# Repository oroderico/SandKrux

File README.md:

Este repositório é um fork do projeto original criado por [sandman21vs](https://github.com/sandman21vs).

Repositório original:
https://github.com/sandman21vs/SandKrux

Crédito integral ao autor original. Este mirror foi publicado para fins de preservação/disponibilidade do projeto.

Todas as licenças, créditos e avisos originais foram mantidos.
 
# SandKrux

Placa de desenvolvimento baseada no chip **K210**, com entradas para **touch**, **câmera** e **LCD grande**, criada especificamente para rodar o firmware **Krux**.

## Status do projeto
**Em desenvolvimento — não finalizado.**  
Este repositório está em evolução. Mudanças podem ocorrer sem aviso.

## Foto da placa
Coloque a imagem em `docs/placa.jpg` (ou ajuste o caminho abaixo).

## Firmware alvo
Este hardware está sendo desenvolvido para o firmware Krux:
- https://github.com/selfcustody/krux

## Como colaborar
Contribuições da comunidade são muito bem-vindas.  
Abra issues, discuta melhorias e proponha alterações.

## Licença
GPLv3.

## Nota sobre fabricação e apoio ao Krux
Se no futuro você pretender **fabricar e vender** este dispositivo, fica o pedido de doar **ao menos 1%** do valor dos dispositivos para a equipe de desenvolvimento do Krux.  
Este é um projeto open-source e, sem o trabalho deles, nada disso existiria.

## Agradecimentos
Obrigado à comunidade e à equipe do Krux pelo trabalho que torna este projeto possível.

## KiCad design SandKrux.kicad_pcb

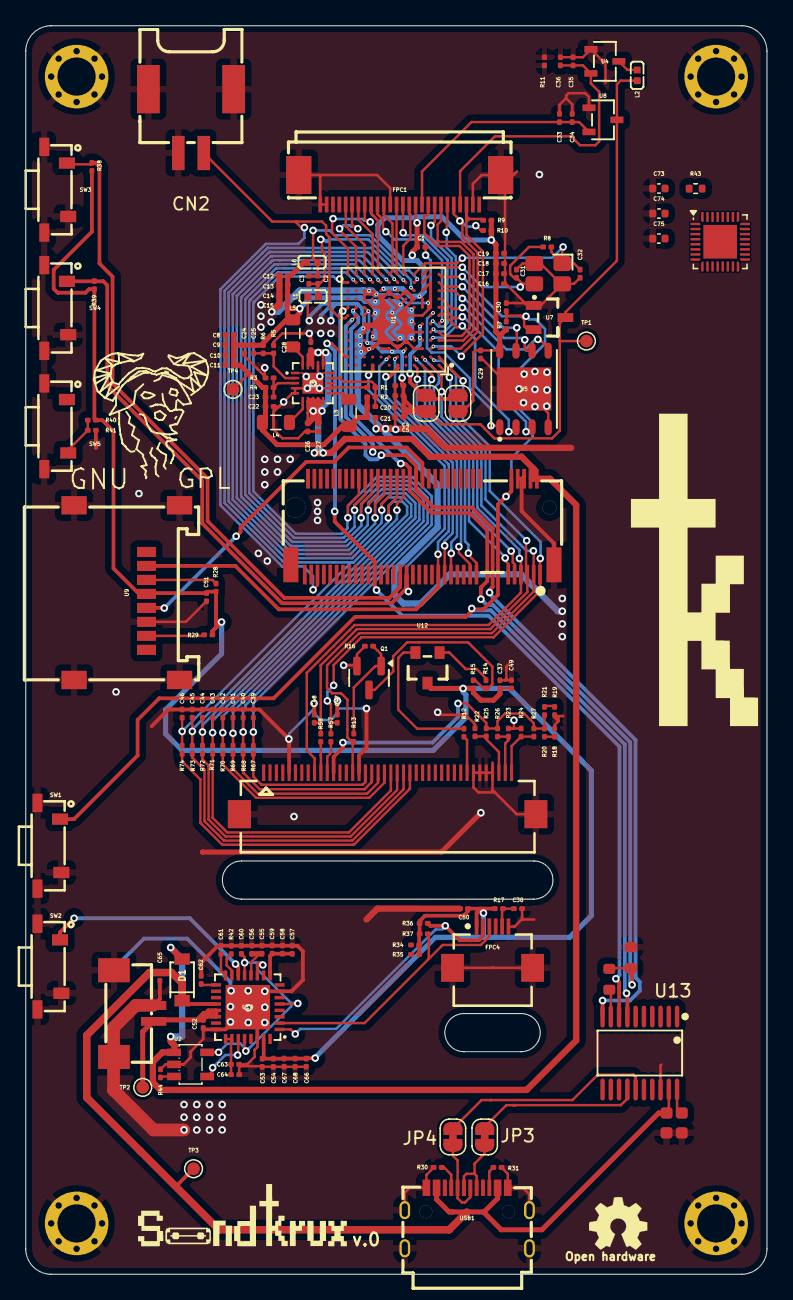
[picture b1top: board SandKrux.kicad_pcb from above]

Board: 2 copper layers, 58.3 x 98.2 mm, 173 parts (0 on the bottom side), 118 nets.

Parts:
C1, C60, C62: 1uF; C_0201_0603Metric
C2, C4, C5, C6, C7, C18, C19, C29, C30, C34, C38, C49, C56: 100nF; C_0201_0603Metric
C3, C8, C9, C10, C11, C12, C13, C14, C15, C16, C17, C33, C36, C37, C50, C51, C53, C55, C58, C65: 10uF; C_0201_0603Metric
C20, C23, C25: 18pF; C_0201_0603Metric
C21, C22, C24, C26, C27, C28, C35, C52, C57, C59, C64, C66, C67, C68: 22uF; C_0201_0603Metric
C31, C32: 6pF; C_0201_0603Metric
C39, C40, C41, C42, C43, C44, C45, C46, C47, C48: 100pF; C_0201_0603Metric
C54: 1nF; C_0201_0603Metric
C61: 220uF; C_0201_0603Metric
C63: 220nF; C_0201_0603Metric
C73, C74, C75: 100n; C_0402_1005Metric
C77: 22uF; C_0603
C79: 10uF; C_0603
CN2: SM02B-PASS-TBT(LF)(SN); CONN-SMD_SM02B-PASS-TBT
CN3: 1.25mm-2P socket; CONN-SMD_1.25T-2P
D1: 1N5819HW-7-F; SOD-123_L2.7-W1.6-LS3.7-RD
FPC1: 05A20L26P; FPC-SMD_05A20L26P
FPC3: FH12-40S-0.5SH(55); FPC-SMD_FH12-40S-0.5SH-55
FPC4: FH12-6S-0.5SH(55); FPC-SMD_FH12-6S-0.5SH-55
H1, H2, H3, H4: Hole, 3mm
IC1: TROPIC01_chip; QFN-32-1EP_4x4mm_P0.4mm_EP2.65x2.65mm
JP1, JP2: SolderJumper_2_Open; SolderJumper-2_P1.3mm_Open_RoundedPad1.0x1.5mm
JP3, JP4: SolderJumper_2_Bridged; SolderJumper-2_P1.3mm_Bridged_RoundedPad1.0x1.5mm
L1, L2, L6: CBW100505U601T; L0402
L3, L4, L5: 2.2uH; L_0805_2012Metric
Q1: S8050; Q_SOT-23
R1, R6: 300k 1%; R_0201_0603Metric
R2, R3, R5: 150k 1%; R_0201_0603Metric
R4: 680k 1%; R_0201_0603Metric
R7: 12K; R_0201_0603Metric
R8: 1M; R_0201_0603Metric
R9, R10: 2K; R_0201_0603Metric
R11, R18, R21, R41: 0R; R_0201_0603Metric
R12: 5.1R; R_0201_0603Metric
R13, R14, R57, R58, R67, R68, R69, R70, R71, R72, R73, R74: 100R; R_0201_0603Metric
R15, R16, R17, R28, R29, R44: 10K; R_0201_0603Metric
R19, R20, R22, R23, R27, R40: NC; R_0201_0603Metric
R24, R25, R26, R30, R31: 5.1K; R_0201_0603Metric
R32, R33: 1kΩ; R_0603
R34, R35, R36, R37, R38, R39: 1.5K; R_0201_0603Metric
R42: 200K; R_0201_0603Metric
R43: 47k; R_0402_1005Metric
SW1, SW2, SW3, SW4, SW5: TL3330AF130QG; SW-SMD_E-SWITCH_TL3330
Sign_OSHW_7.3x6.0mm: Sign_OSHW_7.3x6.0mm; Sign_OSHW_7.3x6.0mmn
TP1, TP2, TP3, TP4: TestPoint_Small; TestPoint_Pad_D1.0mm
U1: K210_C913414; BGA-144_L8.0-W8.0-R12-C12-P0.65-BL
U2: MT9700; SOT-23-5_L3.0-W1.7-P0.95-LS2.8-BR
U3: XC6206-3.3V; SSOT-3_L2.9-W1.6-P0.95-LS2.8-BR
U4: XC6206P182MR_C347373; SOT-23-3_L3.0-W1.7-P0.95-LS2.9-BR
U5: GD25LQ128EWIGR; WSON-8_L6.0-W5.0-P1.27-BL-EP
U6: TMI7003C; QFN-20_L3.0-W3.0-P0.40-BL-EP1.7
U7: SGM803-TXN3/TR_C5152602; SOT-23-3_L2.9-W1.5-P1.90-LS2.6-BR
U8: XC6206P302MR_C347375; SOT-23-3_L3.0-W1.7-P0.95-LS2.9-BR
U9: HX TF-CARD XG8P H1.5; TF-SMD_HX-TF-CARD-XG8P-H1.5
U10: AXP173_C3345106; QFN-32_L5.0-W5.0-P0.50-TL-EP3.5-1
U12: PCIE-67P42H; PCIE-SMD_75P-P0.50_HYC01B-05NGFF-420
U13: CH552T; TSSOP-20_L6.5-W4.4-P0.65-LS6.4-BL
USB1: HYCW412-USBC16-065B; USB-C-SMD_HYCW412-USBC16-065B
X1: X322526MMB4SI; CRYSTAL-SMD_4P-L3.2-W2.5-BL

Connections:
+3.3V: C4.2, C5.2, C6.2, C7.2, JP2.1 (A), L2.2, TP1.1, U1.C5 (VDDIO5B), U1.C7 (VDDIO4B), U1.C8 (VDDIO3B), U1.D10 (VDDIO2A), U1.G10 (VDDIO1A), U1.H10 (VDDIO0A), U7.3 (VCC), U8.3 (VIN)
/3V3: C37.1, C49.1, C50.1, C51.2, C53.2, C54.2, C66.2, C67.2, C68.2, FPC4.1, R15.2, R17.1, R28.2, R29.2, R34.2, R35.2, R36.1, R37.1, R38.1, R39.1, R40.2, U3.3 (VIN), U9.4 (VDD), U10.31 (DCDC1)
/5V: C26.2, C27.2, C28.2, D1.2 (A), U2.1 (VOUT), U6.7 (VIN2), U6.8 (EN2), U6.9 (EN1), U6.10 (VIN1), U6.16 (NC), U6.18 (EN3), U6.19 (VIN3), U12.2, U12.4
/5V_USB: C65.1, C79.1, D1.1 (K), TP3.1, U10.20 (ACIN), U13.19 (VCC/VDD), USB1.A4B9 (VBUS), USB1.B4A9 (VBUS)
/ADD_3V0: C57.2, C58.2, C59.2, U10.9 (LDO3)
/BOOT: U1.B12 (IO_16), U12.53, U13.8 (P1.1/T2EX/CAP2/TIN1/VBUS2/AIN0)
/CAPTOUCH_RST: C38.1, FPC4.5, R17.2
/CC1_2: R30.2, USB1.A5 (CC1)
/CC2_2: R31.2, USB1.B5 (CC2)
/CH552_P1.0: C30.2, R7.2, SW1.1, U1.M1 (~RESET), U7.2 (~RESET), U12.10, U13.7 (P1.0/T2/CAP1/TIN0)
/CH552_RX0: U1.H12 (IO_5), U12.40, U13.10 (P3.0/PWM1_/RXD)
/CH552_TX0: R32.1, U13.9 (P3.1/PWM2_/TXD)
/EXTEN: U2.4 (EN), U10.27 (EXTEN)
/I2C_SCL: FPC4.3, R37.2, U10.2 (SCK)
/I2C_SDA: FPC4.2, R36.2, U10.1 (SDA)
/I2S2_SDI: U1.A3 (IO_35), U12.11
/I2S2_SDOD: U1.B3 (IO_34), U12.9
/IM0: FPC3.38, R22.1, R25.1
/IM1: FPC3.39, R23.1, R26.1
/IM2: FPC3.40, R24.1, R27.1
/IPSOUT: C60.1, U2.5 (VIN), U10.5 (VIN2), U10.11 (LDOIN), U10.13 (APS), U10.28 (VIN1)
/ISET: R44.2, U2.3 (SET)
/ISP_RX: R32.2, R33.1, U1.H11 (IO_4), U12.42
/KEY1: R39.2, SW4.1, U1.A9 (IO_23), U12.43
/KEY2: R38.2, SW3.1, U12.45
/LCD_BACKLIGHT: R12.2, U3.2 (VOUT)
/LCD_CS: FPC3.9, U1.A2 (IO_36), U12.7
/LCD_D0: C39.1, R67.2, U1.L12 (SPI0_D0), U12.58
/LCD_D1: C40.1, R68.2, U1.L11 (SPI0_D1), U12.56
/LCD_D2: C41.1, R69.2, U1.L10 (SPI0_D2), U12.54
/LCD_D3: C42.1, R70.2, U1.L9 (SPI0_D3), U12.52
/LCD_D4: C43.1, R71.2, U1.L8 (SPI0_D4), U12.50
/LCD_D5: C44.1, R72.2, U1.L7 (SPI0_D5), U12.48
/LCD_D6: C45.1, R73.2, U1.L6 (SPI0_D6), U12.46
/LCD_D7: C46.1, R74.2, U1.L5 (SPI0_D7), U12.44
/LCD_DC: C48.1, R58.2, U1.B2 (IO_38), U12.5
/LCD_RST: FPC3.15, R13.1, U1.A1 (IO_37), U12.3
/LCD_WR: C47.1, R57.2, U1.B1 (IO_39), U12.1
/PIN21: U1.B4 (IO_32), U12.21
/PIN23: U1.A4 (IO_33), U12.23
/PRINTER: CN2.1, U1.G12 (IO_7), U12.71
/PWRON: SW2.1, U10.14 (PWRON)
/SPI1_CS_TF: U1.B7 (IO_26), U9.2 (CD/DAT3), U12.33
/SPI1_MISO: U1.G11 (IO_6), U9.5 (CLK), U12.38
/SPI1_MOSI: R28.1, U9.3 (CMD)
/USBDM: JP4.1 (A), USB1.A7 (DN1), USB1.B7 (DN2)
/USBDP: JP3.1 (A), USB1.A6 (DP1), USB1.B6 (DP2)
/USB_D+: U1.B6 (IO_28), U12.29
/USB_D-: U1.A6 (IO_29), U12.31
/VBAT: C52.2, CN3.1, TP2.1, U10.21 (BAT), U10.22 (BAT)
/VCC_1V83V3: FPC3.12, R20.2, R21.2, R25.2, R26.2, R27.2
/VCC_6: R18.1, R20.1
/VCC_7: R19.1, R21.1
/VDD: C55.1, C56.1, U10.12 (LDO4)
/k210/0V9: C8.2, C9.2, C10.2, C11.2, C12.2, C13.2, C14.2, C15.2, C20.2, C21.2, C22.2, C23.2, C24.2, C25.2, L3.1, L4.1, L5.1, L6.2, R2.1, R4.1, R6.1, TP4.1, U1.D4 (VDD), U1.D6 (VDD), U1.D9 (VDD), U1.E7 (VDD), U1.E9 (VDD), U1.F4 (VDD), U1.F6 (VDD), U1.G7 (VDD), U1.G9 (VDD), U1.H4 (VDD), U1.H6 (VDD), U1.J5 (VDD), U1.J7 (VDD), U1.J9 (VDD)
/k210/1V8: C1.1, C16.2, C17.2, C18.2, C19.2, C29.1, FPC1.11, JP1.2 (B), R7.1, R9.2, R10.2, U1.H3 (VDDIO18), U1.J3 (VDDOTP), U1.K6 (VDDIO18), U1.K8 (VDDIO18), U5.8 (VCC)
/k210/26M_OUT: U1.L3 (OSC_CLK), U1.M2 (CLK)
/k210/CMOS-AVDD: C35.2, C36.2, FPC1.4, U4.2 (VOUT)
/k210/CMOS-DVDD: C33.2, C34.2, FPC1.10, U8.2 (VOUT)
/k210/DVP_D0: FPC1.19, U1.M12 (DVP_D0)
/k210/DVP_D1: FPC1.21, U1.M11 (DVP_D1)
/k210/DVP_D2: FPC1.22, U1.M10 (DVP_D2)
/k210/DVP_D3: FPC1.20, U1.M9 (DVP_D3)
/k210/DVP_D4: FPC1.18, U1.M8 (DVP_D4)
/k210/DVP_D5: FPC1.16, U1.M7 (DVP_D5)
/k210/DVP_D6: FPC1.14, U1.M6 (DVP_D6)
/k210/DVP_D7: FPC1.12, U1.M5 (DVP_D7)
/k210/DVP_HSYNC: FPC1.9, U1.E1 (IO_45)
/k210/DVP_PCLK: FPC1.17, U1.F1 (IO_47)
/k210/DVP_PWDN: FPC1.8, U1.E2 (IO_44)
/k210/DVP_RST: FPC1.6, U1.D2 (IO_42)
/k210/DVP_SCL: FPC1.5, R10.1, U1.C1 (IO_41)
/k210/DVP_SDA: FPC1.3, R9.1, U1.C2 (IO_40)
/k210/DVP_VSYNC: FPC1.7, U1.D1 (IO_43)
/k210/DVP_XCLK: FPC1.13, U1.F2 (IO_46)
/k210/F_CLK: U1.K1 (F_CLK), U5.6 (SCLK)
/k210/F_CS: U1.G2 (F_CS), U5.1 (~CS)
/k210/F_D0: U1.J1 (F_D0), U5.5 (SI(IO0))
/k210/F_D1: U1.G1 (F_D1), U5.2 (SO(IO1))
/k210/F_D2: U1.H1 (F_D2), U5.3 (WP#(IO2))
/k210/F_D3: U1.L1 (F_D3), U5.7 (HOLD#(IO3))
/k210/Vadj: C20.1, R1.1, R2.2, U6.14 (FB1)
/k210/Vb: JP1.1 (A), JP2.2 (B), U1.D3 (VDDIO6C), U1.F3 (VDDIO7C)
/k210/XIN: C32.2, R8.2, U1.M4 (XTAL_IN), X1.1 (OSC)
/k210/XOUT: C31.1, R8.1, U1.M3 (XTAL_OUT), X1.3 (OSC)
GND: C1.2, C4.1, C5.1, C6.1, C7.1, C8.1, C9.1, C10.1, C11.1, C12.1, C13.1, C14.1, C15.1, C16.1, C17.1, C18.1, C19.1, C21.1, C22.1, C24.1, C26.1, C27.1, C28.1, C29.2, C30.1, C31.2, C32.1, C33.1, C34.1, C35.1, C36.1, C37.2, C38.2, C39.2, C40.2, C41.2, C42.2, C43.2, C44.2, C45.2, C46.2, C47.2, C48.2, C49.2, C50.2, C51.1, C52.1, C53.1, C54.1, C55.2, C56.2, C57.1, C58.1, C59.1, C60.2, C61.2, C62.2, C63.2, C64.2, C65.2, C66.1, C67.1, C68.1, C73.1, C74.1, C75.1, C77.2, C79.2, CN2.2, CN2.3, CN2.4, CN3.0, CN3.2, FPC1.2, FPC1.15, FPC1.25, FPC1.26, FPC1.27, FPC1.28, FPC3.5, FPC3.16, FPC3.34, FPC3.35, FPC3.36, FPC3.37, FPC3.41 (MH1), FPC3.42 (MH2), FPC4.6, FPC4.7, FPC4.8, H1.1, H2.1, H3.1, H4.1, L1.2, Q1.2 (E), R1.2, R3.2, R5.2, R11.1, R11.2, R16.1, R18.2, R19.2, R22.2, R23.2, R24.2, R30.1, R31.1, R33.2, R41.2, R42.1, R44.1, SW1.2, SW1.3, SW1.4, SW2.2, SW2.3, SW2.4, SW3.2, SW3.3, SW3.4, SW4.2, SW4.3, SW4.4, SW5.3, SW5.4, U1.C3 (VSS), U1.C4 (VSS), U1.C6 (VSS), U1.C9 (VSS), U1.C10 (VSS), U1.D5 (VSS), U1.D7 (VSS), U1.D8 (VSS), U1.E3 (VSS), U1.E4 (VSS), U1.E5 (VSS), U1.E6 (VSS), U1.E8 (VSS), U1.E10 (VSS), U1.F5 (VSS), U1.F7 (VSS), U1.F8 (VSS), U1.F9 (VSS), U1.F10 (VSS), U1.G3 (VSS), U1.G4 (VSS), U1.G5 (VSS), U1.G6 (VSS), U1.G8 (VSS), U1.H2 (VSS), U1.H5 (VSS), U1.H7 (VSS), U1.H8 (VSS), U1.H9 (VSS), U1.J2 (VSS), U1.J4 (VSS), U1.J6 (VSS), U1.J8 (VSS), U1.J10 (VSS), U1.K2 (VSS), U1.K3 (VSS), U1.K5 (VSS), U1.K7 (VSS), U1.K9 (VSS), U1.K10 (VSS), U1.L2 (VSS), U2.2 (GND), U4.1 (VSS), U5.4 (VSS), U5.9 (EP), U6.1 (NC), U6.4 (NC), U6.5 (NC), U6.12 (NC), U6.13 (NC), U6.15 (NC), U6.17 (NC), U6.21 (EP), U7.1 (GND), U8.1 (VSS), U9.6 (VSS2), U9.9 (GND), U9.10 (GND), U9.11 (GND), U9.12 (GND), U10.7 (PGND2), U10.24 (TS), U10.30 (PGND1), U10.33 (EP), U12.6, U12.8, U12.76, U12.77, U13.18 (GND/VSS), USB1.13, USB1.14, USB1.15, USB1.16, USB1.A1B12 (GND), USB1.B1A12 (GND), X1.2 (GND), X1.4 (GND)
unnamed: C63.1, C64.1, U10.25 (IPSOUT), U10.26 (IPSOUT)
unnamed: FPC3.10, R58.1
unnamed: FPC3.11, R57.1
unnamed: FPC3.17, R67.1
unnamed: FPC3.18, R68.1
unnamed: FPC3.19, R69.1
unnamed: FPC3.20, R70.1
unnamed: FPC3.21, R71.1
unnamed: FPC3.22, R72.1
unnamed: FPC3.23, R73.1
unnamed: FPC3.24, R74.1
unnamed: FPC3.33, R12.1
unnamed: JP3.2 (B), U13.14 (P3.6/UDP)
unnamed: JP4.2 (B), U13.15 (P3.7/UDM)
unnamed: Q1.1 (B), R13.2, R16.2
unnamed: Q1.3 (C), R14.1, R15.1
unnamed: R40.1, R41.1, SW5.2
unnamed: C2.2, C3.2, L6.1, U1.L4 (VDDPLL)
unnamed: C2.1, C3.1, L1.1, U1.K4 (VSSPLL)
unnamed: R14.2, U3.1 (VSS)
unnamed: L2.1, U4.3 (VIN)
unnamed: C23.1, R3.1, R4.2, U6.3 (FB2)
unnamed: C25.1, R5.1, R6.2, U6.2 (FB3)
unnamed: L3.2, U6.11 (SW1)
unnamed: L4.2, U6.6 (SW2)
unnamed: L5.2, U6.20 (SW3)
unnamed: R29.1, U9.7 (DAT0)
unnamed: R42.2, U10.15 (BIAS)
unnamed: C62.1, U10.17 (VINT)
unnamed: C61.1, U10.16 (VREF)
unnamed: C77.1, U13.20 (V33)
VCC: C73.2, C74.2, C75.2, R43.2

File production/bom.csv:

Designator,Footprint,Quantity,Value,LCSC Part #
"C1, C60, C62",0201,3,1uF,
"C10, C11, C12, C13, C14, C15, C16, C17, C3, C33, C36, C37, C50, C51, C53, C55, C58, C65, C69, C70, C8, C9",0201,22,10uF,
"C18, C19, C2, C29, C30, C34, C38, C4, C49, C5, C56, C6, C7",0201,13,100nF,
"C20, C23, C25, C71, C72",0201,5,18pF,
"C21, C22, C24, C26, C27, C28, C35, C52, C57, C59, C64, C66, C67, C68",0201,14,22uF,
"C31, C32",0201,2,6pF,
"C39, C40, C41, C42, C43, C44, C45, C46, C47, C48",0201,10,100pF,
C54,0201,1,1nF,
C61,0201,1,220uF,
C63,0201,1,220nF,
"C73, C74, C75",0402,3,100n,
CN2,CONN-SMD_1.25T-2P,1,1.25mm-2P socket,C43462
D1,SOD-123_L2.7-W1.6-LS3.7-RD,1,1N5819HW-7-F,C82544
FPC1,FPC-SMD_05A20L26P,1,05A20L26P,C25503114
FPC3,FPC-SMD_FH12-40S-0.5SH-55,1,FH12-40S-0.5SH(55),C202114
FPC4,FPC-SMD_FH12-6S-0.5SH-55,1,FH12-6S-0.5SH(55),C202118
"H1, H2, H3, H4","Hole, 3mm",4,~,
IC1,QFN-32-1EP_4x4mm_P0.4mm_EP2.65x2.65mm,1,TROPIC01_chip,
"L1, L2, L6",L0402,3,CBW100505U601T,C124083
"L3, L4, L5",0805,3,2.2uH,
"LED1, LED2",LED0603-RD,2,KT-0603R,C2286
Q1,Q_SOT-23,1,S8050,C364312
"R1, R6",0201,2,300k 1%,
"R10, R9",0201,2,2K,
"R11, R18, R21, R41",0201,4,0R,
R12,0201,1,5.1R,
"R13, R14, R57, R58, R67, R68, R69, R70, R71, R72, R73, R74",0201,12,100R,
"R15, R16, R17, R28, R29, R44, R54",0201,7,10K,
"R19, R20, R22, R23, R27, R40, R55",0201,7,NC,
"R2, R3, R5",0201,3,150k 1%,
"R24, R25, R26, R30, R31, R53, R56",0201,7,5.1K,
"R34, R35, R36, R37, R38, R39, R46, R49",0201,8,1.5K,
R4,0201,1,680k 1%,
R42,0201,1,200K,
R43,0402,1,47k,
R45,0201,1,1.5,
"R47, R48, R50, R51, R52",0201,5,22R,
R7,0201,1,12K,
R8,0201,1,1M,
"SW1, SW2, SW3, SW4, SW5",SW-SMD_E-SWITCH_TL3330,5,TL3330AF130QG,C2886885
"TP1, TP2, TP3, TP4",TestPoint_Pad_D1.0mm,4,TestPoint_Small,
U1,BGA-144_L8.0-W8.0-R12-C12-P0.65-BL,1,K210_C913414,C913414
U10,QFN-32_L5.0-W5.0-P0.50-TL-EP3.5-1,1,AXP173_C3345106,C3345106
U11,WQFN-28_L4.0-W4.0-P0.40-BL-EP,1,GD32F150G8U6,C84216
U12,PCIE-SMD_75P-P0.50_HYC01B-05NGFF-420,1,PCIE-67P42H,C19188865
U2,SOT-23-5_L3.0-W1.7-P0.95-LS2.8-BR,1,MT9700,C89855
U3,SSOT-3_L2.9-W1.6-P0.95-LS2.8-BR,1,XC6206-3.3V,C2891841
U4,SOT-23-3_L3.0-W1.7-P0.95-LS2.9-BR,1,XC6206P182MR_C347373,C347373
U5,WSON-8_L6.0-W5.0-P1.27-BL-EP,1,GD25LQ128EWIGR,C2928889
U6,QFN-20_L3.0-W3.0-P0.40-BL-EP1.7,1,TMI7003C,C840566
U7,SOT-23-3_L2.9-W1.5-P1.90-LS2.6-BR,1,SGM803-TXN3/TR_C5152602,C5152602
U8,SOT-23-3_L3.0-W1.7-P0.95-LS2.9-BR,1,XC6206P302MR_C347375,C347375
U9,TF-SMD_HX-TF-CARD-XG8P-H1.5,1,HX TF-CARD XG8P H1.5,C19189039
USB1,USB-C-SMD_HYCW412-USBC16-065B,1,HYCW412-USBC16-065B,C5342196
"X1, X2",CRYSTAL-SMD_4P-L3.2-W2.5-BL,2,X322526MMB4SI,C15192

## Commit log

2026-03-03 muito trabalho to quase acabando
2026-03-07 CH552T
2026-03-07 teste
2026-03-07 ajuste de esquematico e posicionamento de componentes
2026-03-07 CNC AND PRINTER
